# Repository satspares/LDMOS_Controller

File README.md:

# LDMOS_Controller
LDMOS Controller with DWIN Display
New October 2026

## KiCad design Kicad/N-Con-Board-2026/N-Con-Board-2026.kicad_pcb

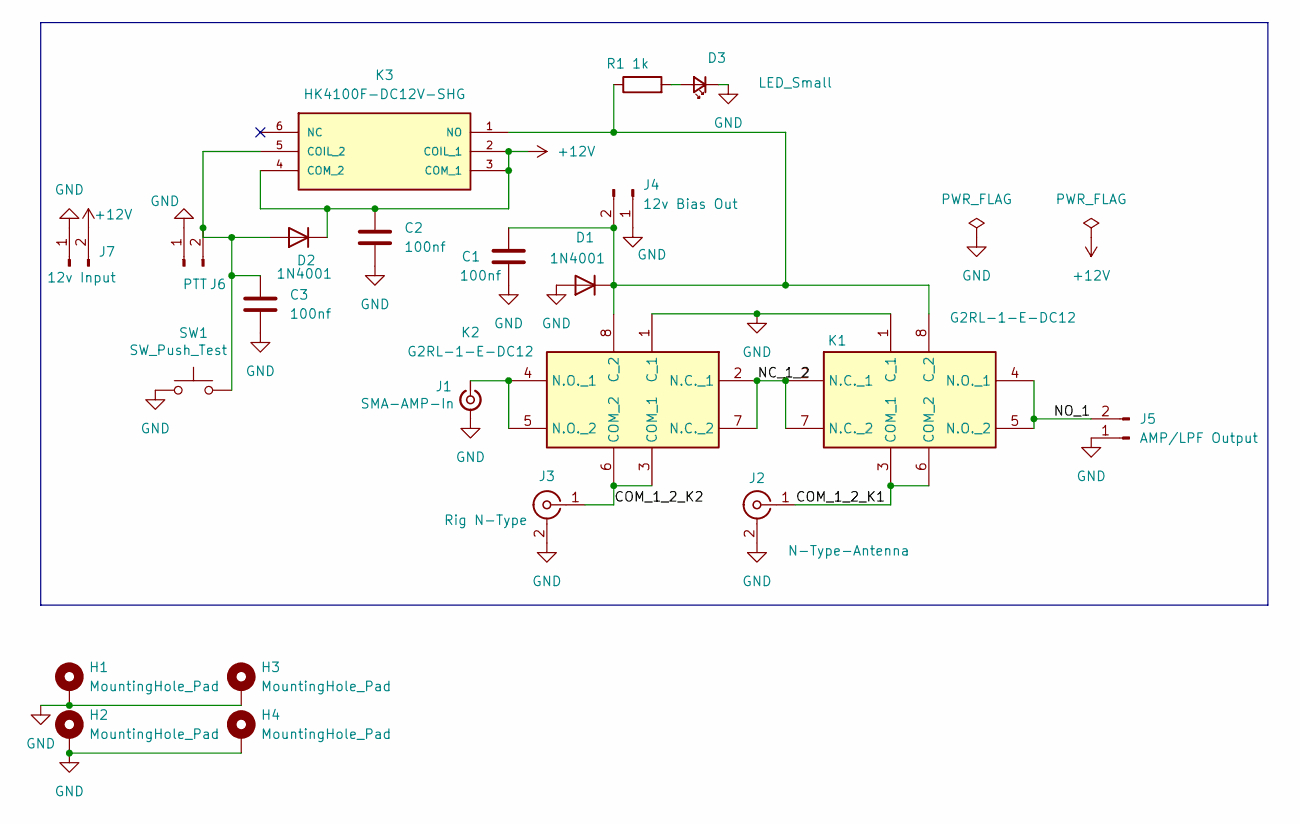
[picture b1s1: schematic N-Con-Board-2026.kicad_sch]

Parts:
C1, C2, C3: 100nf; C_Disc_D6.0mm_W2.5mm_P5.00mm
D1, D2: 1N4001; D_DO-41_SOD81_P10.16mm_Horizontal
D3: LED_Small; LED_D3.0mm
H1, H2, H3, H4: MountingHole_Pad; MountingHole_3.5mm_Pad_Via
J1: SMA-AMP-In; SMA_Amphenol_132134_Vertical
J2: N-Type-Antenna; N_TYPE
J3: Rig N-Type; N_TYPE
J4: 12v Bias Out; JST_EH_B2B-EH-A_1x02_P2.50mm_Vertical
J5: AMP/LPF Output; SolderWirePad_1x02_SMD_11x6mm
J6: PTT; JST_EH_B2B-EH-A_1x02_P2.50mm_Vertical
J7: 12v Input; JST_EH_B2B-EH-A_1x02_P2.50mm_Vertical
K1, K2: G2RL-1-E-DC12; G2RL1EDC24; Mouser Part Number 653-G2RL-1-E-DC12
K3: HK4100F-DC12V-SHG; HK4100FDC5VSHG; MANUFACTURER_PART_NUMBER HK4100F-DC5V-SHG
R1: 1k; R_Axial_DIN0207_L6.3mm_D2.5mm_P7.62mm_Horizontal
SW1: SW_Push_Test; SW_PUSH_6mm

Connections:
+12V: C2.1, D2.1 (K), J7.2, K3.2 (COIL_1), K3.3 (COM_1), K3.4 (COM_2)
/COM_1_2_K1: J2.1 (In), K1.3 (COM_1), K1.6 (COM_2)
/COM_1_2_K2: J3.1 (In), K2.3 (COM_1), K2.6 (COM_2)
/NC_1_2: K1.2 (N.C._1), K1.7 (N.C._2), K2.2 (N.C._1), K2.7 (N.C._2)
/NO_1: J5.2, K1.4 (N.O._1), K1.5 (N.O._2)
GND: C1.2, C2.2, C3.2, D1.2 (A), D3.1 (K), H1.1 (1_1), H2.1 (1_1), H3.1 (1_1), H4.1 (1_1), J1.2 (Ext), J2.2 (Ext), J3.2 (Ext), J4.1, J5.1, J6.1, J7.1, K1.1 (C_1), K2.1 (C_1), SW1.1
unnamed: C1.1, D1.1 (K), J4.2, K1.8 (C_2), K2.8 (C_2), K3.1 (NO), R1.1
unnamed: C3.1, D2.2 (A), J6.2, K3.5 (COIL_2), SW1.2
unnamed: D3.2 (A), R1.2
unnamed: J1.1 (In), K2.4 (N.O._1), K2.5 (N.O._2)

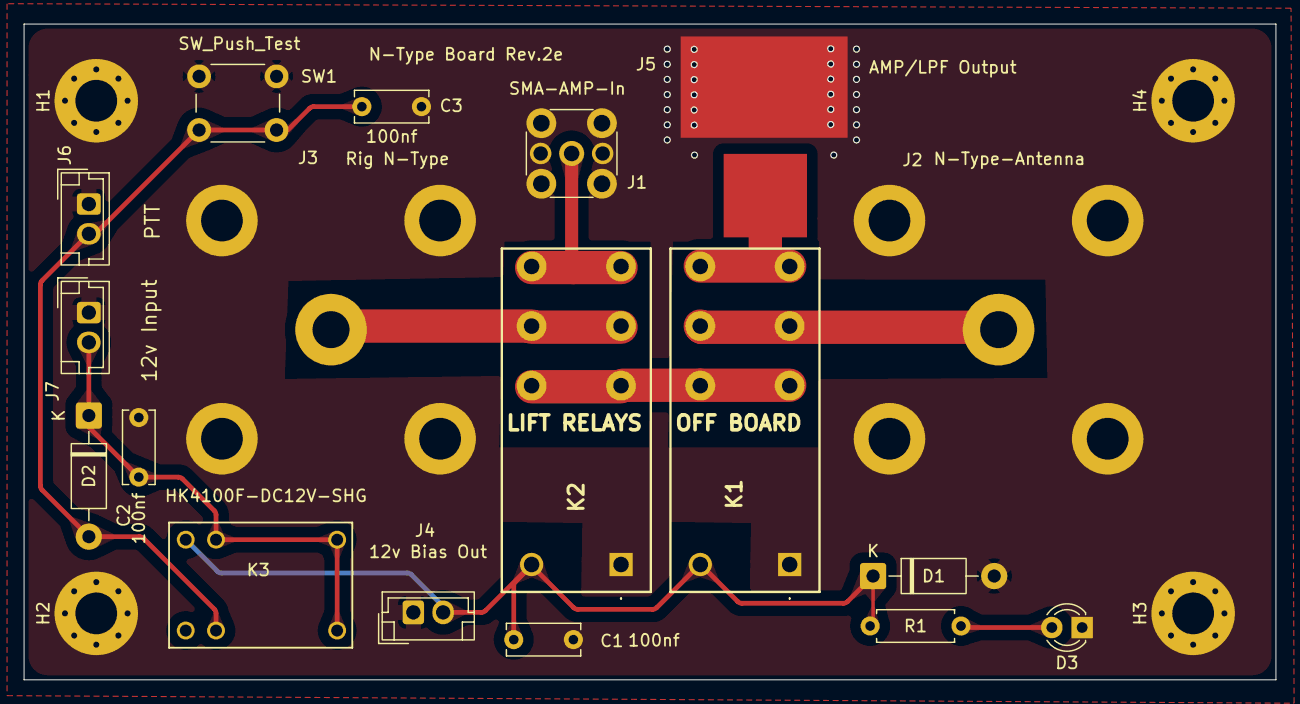
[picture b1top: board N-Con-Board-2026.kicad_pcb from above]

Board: 2 copper layers, 105.0 x 55.0 mm, 22 parts (0 on the bottom side), 10 nets.

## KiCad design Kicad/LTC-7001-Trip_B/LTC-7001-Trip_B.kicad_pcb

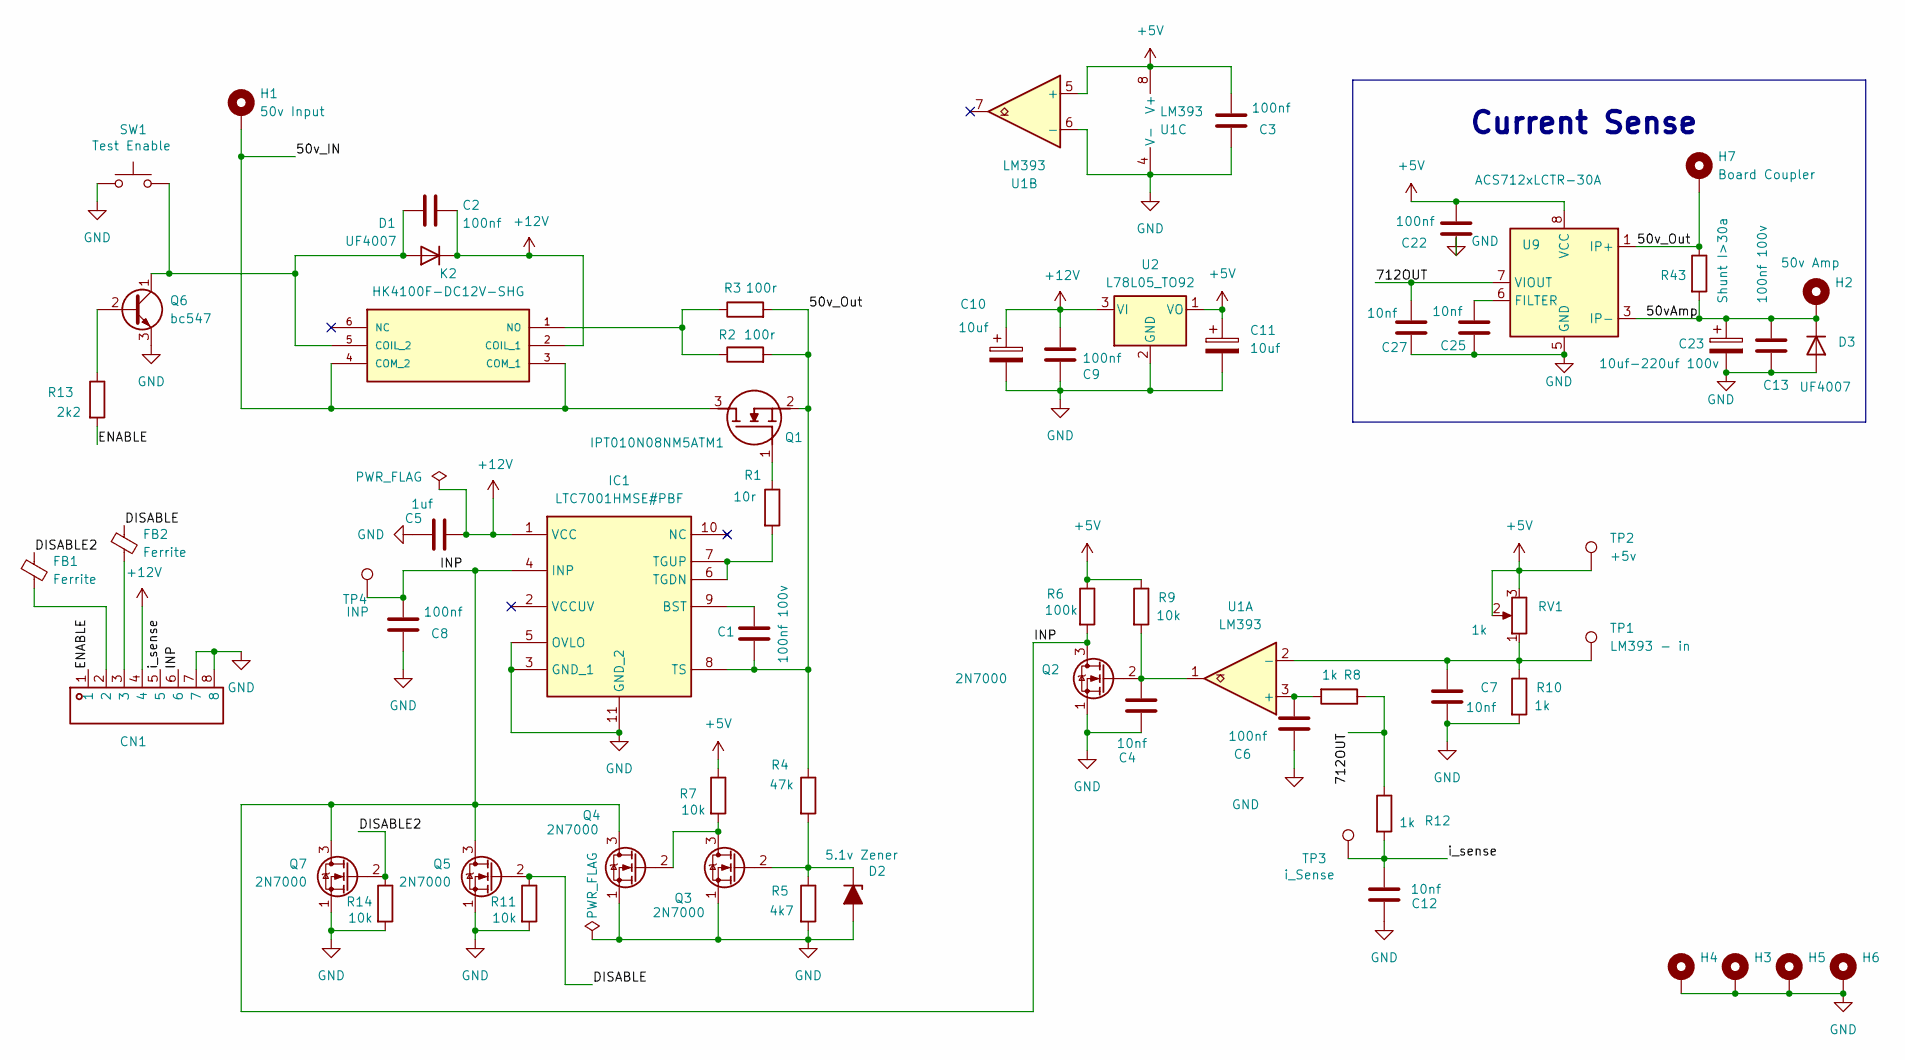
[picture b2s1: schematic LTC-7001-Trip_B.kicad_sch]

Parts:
C1, C13: 100nf 100v; C_Disc_D3.8mm_W2.6mm_P2.50mm
C2, C3, C6, C8, C9, C22: 100nf; C_Disc_D3.8mm_W2.6mm_P2.50mm
C4, C12: 10nf; C_Disc_D3.8mm_W2.6mm_P2.50mm
C5: 1uf; C_Disc_D3.8mm_W2.6mm_P2.50mm
C7, C25, C27: 10nf; C_Disc_D3.4mm_W2.1mm_P2.50mm
C10, C11: 10uf; C_Disc_D3.8mm_W2.6mm_P2.50mm
C23: 10uf-220uf 100v; CP_Radial_D10.0mm_P5.00mm
CN1: CONN-TH_8P-P2.54_KF141R-2.54-8P; Manufacturer Part KF141R-2.54-8P; LCSC Part Name 1x6P 2.54mm 每排P数:8 排数:1
D1, D3: UF4007; D_DO-41_SOD81_P10.16mm_Horizontal
D2: 5.1v Zener; D_DO-35_SOD27_P7.62mm_Horizontal
FB1, FB2: Ferrite; R_1206_3216Metric_Pad1.30x1.75mm_HandSolder
H1: 50v Input; Power-Pad
H2: 50v Amp; Power-Pad
H3, H4, H5, H6: MountingHole_Pad; MountingHole_3.5mm_Pad_Via
H7: Board Coupler; MountingHole_3.5mm_Pad_Via
IC1: LTC7001HMSE#PBF; SOP50P490X110-11N; Manufacturer_Part_Number LTC7001HMSE#PBF; Mouser Part Number 584-LTC7001HMSEPBF
K2: HK4100F-DC12V-SHG; HK4100FDC5VSHG; MANUFACTURER_PART_NUMBER HK4100F-DC5V-SHG
Q1: IPT010N08NM5ATM1; IAUT150N10S5N035ATMA1; Manufacturer_Part_Number FDP083N15A-F102; Mouser Part Number 512-FDP083N15A_F102
Q2, Q3, Q4, Q5, Q7: 2N7000; TO-92-mod2
Q6: bc547; TO-92_HandSolder
R1: 10r; R_Axial_DIN0207_L6.3mm_D2.5mm_P7.62mm_Horizontal
R2, R3: 100r; RESC11050X120N
R4: 47k; R_Axial_DIN0207_L6.3mm_D2.5mm_P7.62mm_Horizontal
R5: 4k7; R_Axial_DIN0207_L6.3mm_D2.5mm_P7.62mm_Horizontal
R6: 100k; R_Axial_DIN0207_L6.3mm_D2.5mm_P7.62mm_Horizontal
R7, R9, R11, R14: 10k; R_Axial_DIN0207_L6.3mm_D2.5mm_P7.62mm_Horizontal
R8, R10, R12: 1k; R_Axial_DIN0207_L6.3mm_D2.5mm_P7.62mm_Horizontal
R13: 2k2; R_Axial_DIN0207_L6.3mm_D2.5mm_P7.62mm_Horizontal
R43: Shunt I>30a; RESC11050X120N
RV1: 1k
SW1: Test Enable; SW_PUSH_6mm
TP1: LM393 - in; TestPoint_THTPad_3.0x3.0mm_Drill1.5mm
TP2: +5v; TestPoint_THTPad_3.0x3.0mm_Drill1.5mm
TP3: i_Sense; TestPoint_THTPad_3.0x3.0mm_Drill1.5mm
TP4: INP; TestPoint_THTPad_3.0x3.0mm_Drill1.5mm
U1: LM393; DIP-8_W7.62mm_Socket
U2: L78L05_TO92; TO-92_Inline-mod
U9: ACS712xLCTR-30A; SOIC-8_3.9x4.9mm_P1.27mm

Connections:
+5V: C3.2, C11.1, C22.1, R6.1, R7.1, R9.1, RV1.2, RV1.3, TP2.1 (1_1), U1.5 (+), U1.8 (V+), U2.1 (VO), U9.8 (VCC)
+12V: C2.2, C5.2, C9.2, C10.1, CN1.4, D1.1 (K), IC1.1 (VCC), K2.2 (COIL_1), U2.3 (VI)
/50vAmp: C13.1, C23.1, D3.1 (K), H2.1 (1_1), R43.2, U9.3 (IP-), U9.4 (IP-)
/50v_IN: H1.1 (1_1), K2.3 (COM_1), K2.4 (COM_2), Q1.3 (S)
/50v_Out: C1.2, H7.1 (1_1), IC1.8 (TS), Q1.2 (D), R2.2, R3.2, R4.1, R43.1, U9.1 (IP+), U9.2 (IP+)
/712OUT: C27.1, R8.1, R12.1, U9.7 (VIOUT)
/DISABLE: FB2.1, Q5.2 (G), R11.1
/DISABLE2: FB1.1, Q7.2 (G), R14.1
/ENABLE: CN1.1, R13.2
/INP: C8.2, CN1.6, IC1.4 (INP), Q2.3 (D), Q4.3 (D), Q5.3 (D), Q7.3 (D), R6.2, TP4.1 (1_1)
/i_sense: C12.1, CN1.5, R12.2, TP3.1 (1_1)
GND: C3.1, C4.1, C5.1, C6.1, C7.1, C8.1, C9.1, C10.2, C11.2, C12.2, C13.2, C22.2, C23.2, C25.1, C27.2, CN1.7, CN1.8, D2.2 (A), D3.2 (A), H3.1 (1_1), H4.1 (1_1), H5.1 (1_1), H6.1 (1_1), IC1.3 (GND_1), IC1.5 (OVLO), IC1.11 (GND_2), Q2.1 (S), Q3.1 (S), Q4.1 (S), Q5.1 (S), Q6.3 (E), Q7.1 (S), R5.2, R10.2, R11.2, R14.2, SW1.1, U1.4 (V-), U1.6 (-), U2.2 (GND), U9.5 (GND)
unnamed: CN1.2, FB1.2
unnamed: CN1.3, FB2.2
unnamed: C2.1, D1.2 (A), K2.5 (COIL_2), Q6.1 (C), SW1.2
unnamed: D2.1 (K), Q3.2 (G), R4.2, R5.1
unnamed: C1.1, IC1.9 (BST)
unnamed: IC1.6 (TGDN), IC1.7 (TGUP), R1.2
unnamed: K2.1 (NO), R2.1, R3.1
unnamed: Q1.1 (G), R1.1
unnamed: C4.2, Q2.2 (G), R9.2, U1.1
unnamed: Q3.3 (D), Q4.2 (G), R7.2
unnamed: Q6.2 (B), R13.1
unnamed: C6.2, R8.2, U1.3 (+)
unnamed: C7.2, R10.1, RV1.1, TP1.1 (1_1), U1.2 (-)
unnamed: C25.2, U9.6 (FILTER)

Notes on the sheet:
Current Sense

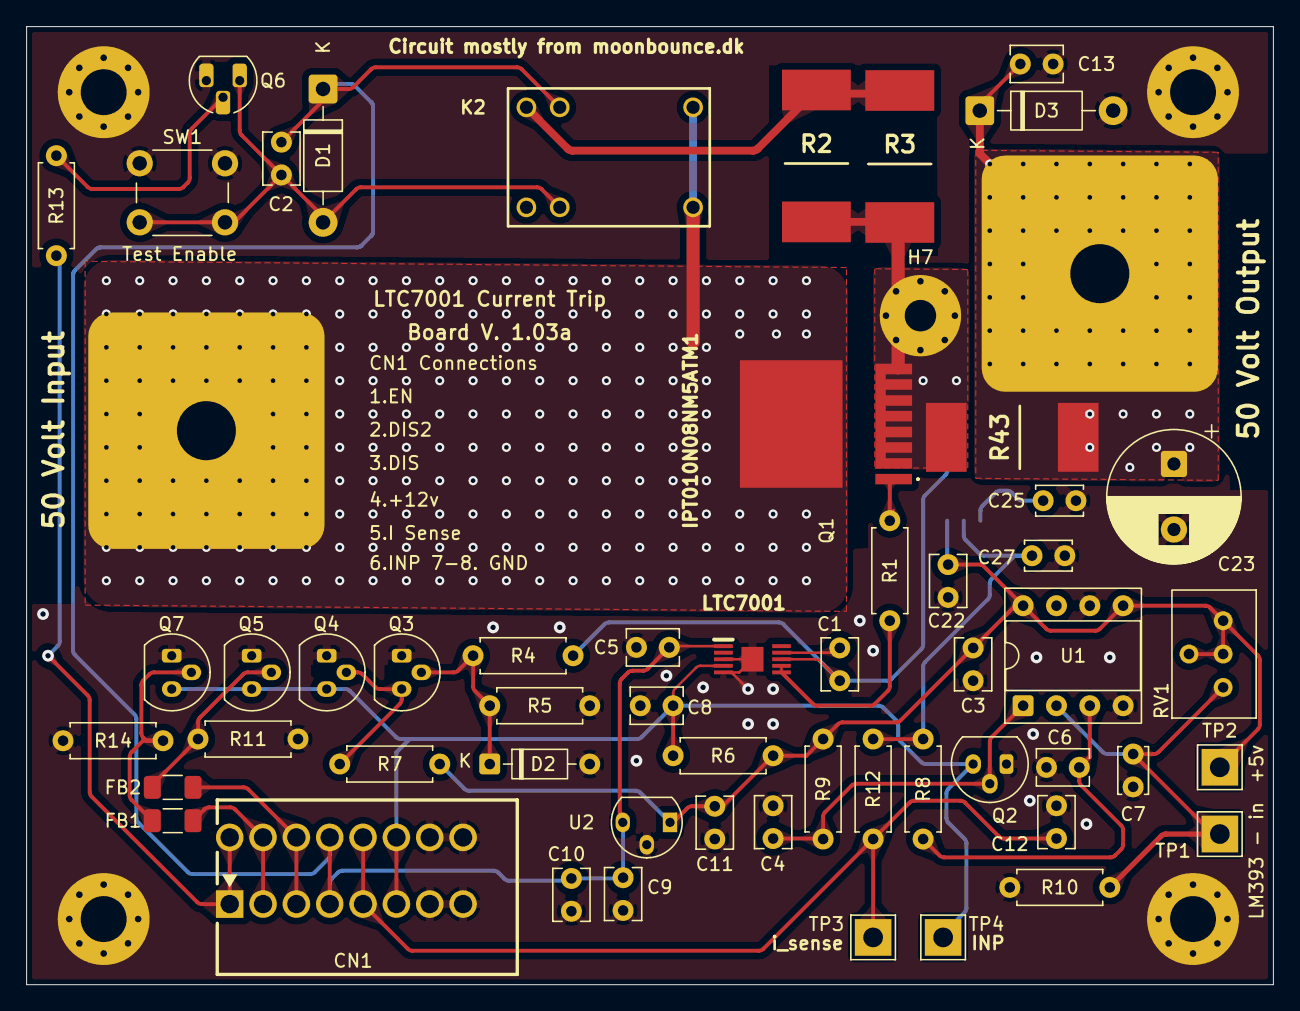
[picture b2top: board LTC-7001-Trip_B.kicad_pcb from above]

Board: 2 copper layers, 95.0 x 73.0 mm, 63 parts (1 on the bottom side), 26 nets.

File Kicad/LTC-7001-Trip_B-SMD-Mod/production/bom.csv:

Designator,Footprint,Quantity,Value,LCSC Part #
"C1, C13",C_Disc_D3.8mm_W2.6mm_P2.50mm,2,100nf 100v,
"C10, C11",C_Disc_D3.8mm_W2.6mm_P2.50mm,2,10uf,
"C12, C4",C_Disc_D3.8mm_W2.6mm_P2.50mm,2,10nf,
"C2, C22, C3, C6, C8, C9",C_Disc_D3.8mm_W2.6mm_P2.50mm,6,100nf,
C23,CP_Radial_D10.0mm_P5.00mm,1,10uf-220uf 100v,
"C25, C27, C7",C_Disc_D3.4mm_W2.1mm_P2.50mm,3,10nf,
C5,C_Disc_D3.8mm_W2.6mm_P2.50mm,1,1uf,
CN1,CONN-TH_8P-P2.54_KF141R-2.54-8P,1,~,
"D1, D3",D_DO-41_SOD81_P10.16mm_Horizontal,2,UF4007,
D2,D_DO-35_SOD27_P7.62mm_Horizontal,1,5.1v Zener,
"FB1, FB2",1206,2,Ferrite,
IC1,SOP50P490X110-11N,1,LTC7001HMSE#PBF,
K2,HK4100FDC5VSHG,1,HK4100F-DC12V-SHG,
Q1,IAUT150N10S5N035ATMA1,1,IPT010N08NM5ATM1,
"Q2, Q3, Q4, Q5, Q7",TO-92-mod2,5,2N7000,
Q6,TO-92_HandSolder,1,bc547,
R1,R_Axial_DIN0207_L6.3mm_D2.5mm_P7.62mm_Horizontal,1,10r,
"R10, R12, R8",R_Axial_DIN0207_L6.3mm_D2.5mm_P7.62mm_Horizontal,3,1k,
"R11, R14, R7, R9",R_Axial_DIN0207_L6.3mm_D2.5mm_P7.62mm_Horizontal,4,10k,
R13,R_Axial_DIN0207_L6.3mm_D2.5mm_P7.62mm_Horizontal,1,2k2,
"R2, R3",RESC11050X120N,2,100r,
R4,R_Axial_DIN0207_L6.3mm_D2.5mm_P7.62mm_Horizontal,1,47k,
R43,RESC11050X120N,1,Shunt I>30a,
R5,R_Axial_DIN0207_L6.3mm_D2.5mm_P7.62mm_Horizontal,1,4k7,
R6,R_Axial_DIN0207_L6.3mm_D2.5mm_P7.62mm_Horizontal,1,100k,
RV1,Potentiometer_Bourns_3296W_Vertical,1,1k,
SW1,SW_PUSH_6mm,1,Test Enable,
TP1,TestPoint_THTPad_3.0x3.0mm_Drill1.5mm,1,LM393 - in,
TP2,TestPoint_THTPad_3.0x3.0mm_Drill1.5mm,1,+5v,
TP3,TestPoint_THTPad_3.0x3.0mm_Drill1.5mm,1,i_Sense,
TP4,TestPoint_THTPad_3.0x3.0mm_Drill1.5mm,1,INP,
U1,SOP-8_3.76x4.96mm_P1.27mm,1,LMV393,
U2,TO-92_Inline-mod,1,L78L05_TO92,
U9,SOIC-8_3.9x4.9mm_P1.27mm,1,ACS712xLCTR-30A,

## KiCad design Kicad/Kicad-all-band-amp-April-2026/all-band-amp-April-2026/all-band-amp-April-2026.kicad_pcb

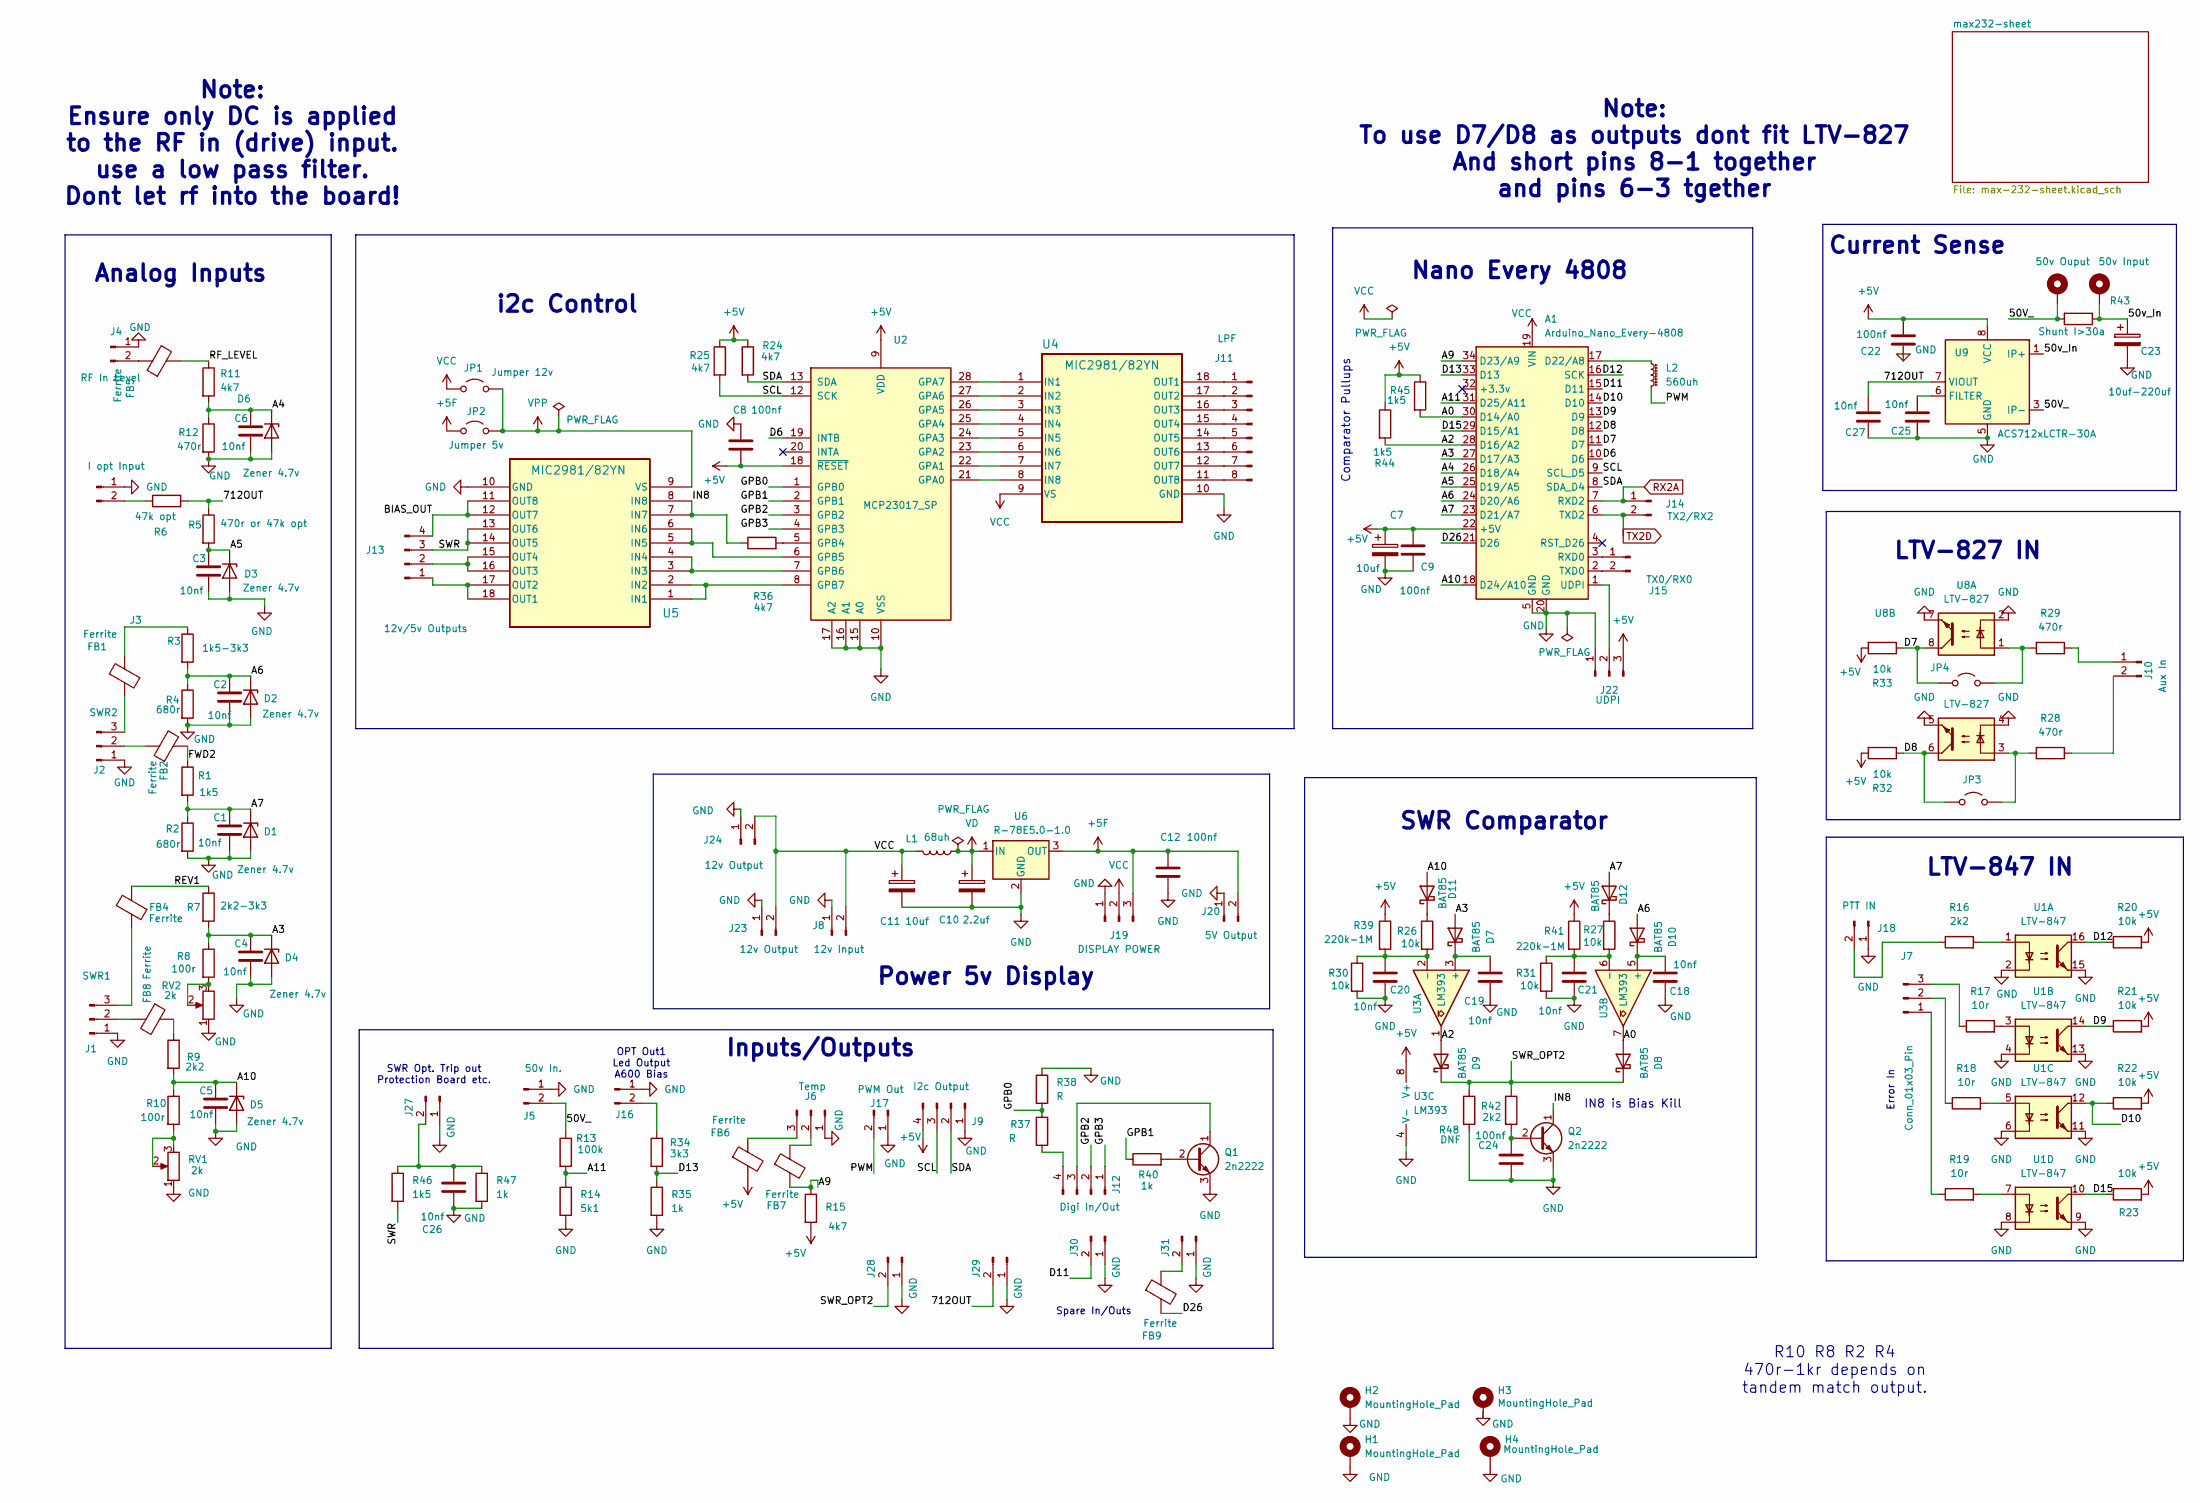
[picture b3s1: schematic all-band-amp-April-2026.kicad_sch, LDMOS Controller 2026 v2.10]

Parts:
A1: Arduino_Nano_Every-4808; DIP-34_W15.24mm
C1, C2, C3, C4, C5, C6, C18, C19, C20, C21, C25, C26, C27: 10nf; C_Disc_D3.4mm_W2.1mm_P2.50mm
C7, C11: 10uf; CP_Radial_D5.0mm_P2.00mm
C8, C9, C12, C22, C24: 100nf; C_Disc_D6.0mm_W2.5mm_P5.00mm
C10: 2.2uf; CP_Radial_D5.0mm_P2.00mm
C23: 10uf-220uf; CP_Radial_D10.0mm_P5.00mm
D1, D2, D3, D4, D5, D6: Zener 4.7v; D_DO-35_SOD27_P7.62mm_Horizontal
D7, D8, D9, D10, D11, D12: BAT85; D_DO-35_SOD27_P7.62mm_Horizontal
FB1, FB2, FB4, FB5, FB6, FB7, FB8, FB9: Ferrite; R_1206_3216Metric_Pad1.30x1.75mm_HandSolder-mod
H1, H2, H3, H4: MountingHole_Pad; MountingHole_3.5mm_Pad_Via
H5: 50v Ouput; PowerPad9mm
H6: 50v Input; PowerPad9mm
J1: SWR1; JST_EH_B3B-EH-A_1x03_P2.50mm_Vertical-mod2
J2: SWR2; JST_EH_B3B-EH-A_1x03_P2.50mm_Vertical-mod2
J3: I opt Input; JST_EH_B2B-EH-A_1x02_P2.50mm_Vertical-Mod
J4: RF In Level; JST_EH_B2B-EH-A_1x02_P2.50mm_Vertical-Mod
J5, J16: 50v In.; JST_EH_B2B-EH-A_1x02_P2.50mm_Vertical-Mod
J6: Temp; JST_EH_B3B-EH-A_1x03_P2.50mm_Vertical-mod2
J7: Conn_01x03_Pin; JST_EH_B3B-EH-A_1x03_P2.50mm_Vertical-mod2
J8: 12v Input; JST_EH_B2B-EH-A_1x02_P2.50mm_Vertical-Mod
J9: I2c Output; JST_EH_B4B-EH-A_1x04_P2.50mm_Vertical-mod2
J10: Aux In; JST_EH_B2B-EH-A_1x02_P2.50mm_Vertical-Mod
J11: LPF; JST_EH_B8B-EH-A_1x08_P2.50mm_Vertical
J12: Digi In/Out; JST_EH_B4B-EH-A_1x04_P2.50mm_Vertical-mod2
J13: 12v/5v Outputs; JST_EH_B4B-EH-A_1x04_P2.50mm_Vertical-mod2
J14: TX2/RX2; JST_EH_B2B-EH-A_1x02_P2.50mm_Vertical-Mod
J15: TX0/RX0; JST_EH_B2B-EH-A_1x02_P2.50mm_Vertical-Mod
J17: PWM Out; JST_EH_B2B-EH-A_1x02_P2.50mm_Vertical-Mod
J18: PTT IN; JST_EH_B2B-EH-A_1x02_P2.50mm_Vertical-Mod
J19: DISPLAY POWER; JST_EH_B3B-EH-A_1x03_P2.50mm_Vertical-mod2
J20: 5V Output; JST_EH_B2B-EH-A_1x02_P2.50mm_Vertical-Mod
J22: UDPI; JST_EH_B3B-EH-A_1x03_P2.50mm_Vertical
J23, J24: 12v Output; JST_EH_B2B-EH-A_1x02_P2.50mm_Vertical-Mod
J27, J28, J29, J30, J31: SWR trip out; JST_EH_B2B-EH-A_1x02_P2.50mm_Vertical-Mod
JP1: Jumper 12v; SolderWire-0.5sqmm_1x02_P4.8mm_D0.9mm_OD2.3mm
JP2: Jumper 5v; SolderWire-0.5sqmm_1x02_P4.8mm_D0.9mm_OD2.3mm
JP3, JP4: Jumper_2_Open; SolderJumper-2_P1.3mm_Open_TrianglePad1.0x1.5mm
L1: 68uh; L_Radial_D7.0mm_P3.00mm
L2: 560uh; L_Axial_L5.3mm_D2.2mm_P7.62mm_Horizontal_Vishay_IM-1
Q1, Q2: 2n2222; TO-92_HandSolder
R1, R44, R45, R46: 1k5; R_Axial_DIN0207_L6.3mm_D2.5mm_P7.62mm_Horizontal
R2, R4: 680r; R_Axial_DIN0207_L6.3mm_D2.5mm_P7.62mm_Horizontal
R3: 1k5-3k3; R_Axial_DIN0207_L6.3mm_D2.5mm_P7.62mm_Horizontal
R5: 470r or 47k opt; R_Axial_DIN0207_L6.3mm_D2.5mm_P7.62mm_Horizontal
R6: 47k opt; R_Axial_DIN0207_L6.3mm_D2.5mm_P7.62mm_Horizontal
R7: 2k2-3k3; R_Axial_DIN0207_L6.3mm_D2.5mm_P7.62mm_Horizontal
R8, R10: 100r; R_Axial_DIN0207_L6.3mm_D2.5mm_P7.62mm_Horizontal
R9, R16, R42: 2k2; R_Axial_DIN0207_L6.3mm_D2.5mm_P7.62mm_Horizontal
R11: 4k7; R_Axial_DIN0204_L3.6mm_D1.6mm_P5.08mm_Horizontal
R12: 470r; R_Axial_DIN0204_L3.6mm_D1.6mm_P5.08mm_Horizontal
R13: 100k; R_Axial_DIN0207_L6.3mm_D2.5mm_P7.62mm_Horizontal
R14: 5k1; R_Axial_DIN0207_L6.3mm_D2.5mm_P7.62mm_Horizontal
R15, R24, R25, R36: 4k7; R_Axial_DIN0207_L6.3mm_D2.5mm_P7.62mm_Horizontal
R17, R18, R19: 10r; R_Axial_DIN0207_L6.3mm_D2.5mm_P7.62mm_Horizontal
R20, R21, R22, R23, R26, R27, R30, R31, R32, R33: 10k; R_Axial_DIN0207_L6.3mm_D2.5mm_P7.62mm_Horizontal
R28, R29: 470r; R_Axial_DIN0207_L6.3mm_D2.5mm_P7.62mm_Horizontal
R34: 3k3; R_Axial_DIN0207_L6.3mm_D2.5mm_P7.62mm_Horizontal
R35, R40, R47: 1k; R_Axial_DIN0207_L6.3mm_D2.5mm_P7.62mm_Horizontal
R37, R38: R; R_Axial_DIN0207_L6.3mm_D2.5mm_P7.62mm_Horizontal
R39, R41: 220k-1M; R_Axial_DIN0207_L6.3mm_D2.5mm_P7.62mm_Horizontal
R43: Shunt I>30a; CHSA3920R0003F-MOD
R48: DNF; R_Axial_DIN0207_L6.3mm_D2.5mm_P7.62mm_Horizontal
RV1, RV2: 2k; Potentiometer_Bourns_3299Y_Vertical
U1: LTV-847; DIP-16_W7.62mm
U2: MCP23017_SP; DIP-28_W7.62mm
U3: LM393; DIP-8_W7.62mm
U4, U5: MIC2981/82YN; DIP-18_W7.62mm_Socket
U6: R-78E5.0-1.0; Converter_DCDC_RECOM_R-78E-0.5_THT
U8: LTV-827; DIP-8_W7.62mm
U9: ACS712xLCTR-30A; SOIC-8_3.9x4.9mm_P1.27mm

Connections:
+5F: C12.1, J19.3, J20.2, JP2.1 (A), U6.3 (OUT); also elsewhere on the board
+5V: A1.22 (+5V), C7.1, C8.2, C9.1, C22.1, FB6.2, J9.4, J22.3, R15.2, R20.2, R21.2, R22.2, R23.2, R24.1, R25.1, R32.2, R33.2, R39.1, R41.1, R44.1, R45.1, U2.9 (VDD), U2.18 (~RESET), U3.8 (V+), U9.8 (VCC)
/50V_: H5.1 (1_1), J5.2, R13.1, R43.2, U9.3 (IP-), U9.4 (IP-)
/50v_In: C23.1, H6.1 (1_1), R43.1, U9.1 (IP+), U9.2 (IP+)
/712OUT: C27.1, J29.2, R5.1, R6.2, U9.7 (VIOUT)
/A0: A1.30 (D14/A0), D8.2 (A), R45.2, U3.7
/A2: A1.28 (D16/A2), D9.2 (A), R44.2, U3.1
/A3: A1.27 (D17/A3), C4.1, D4.1 (K), D7.2 (A), R7.2, R8.1
/A4: A1.26 (D18/A4), C6.1, D6.1 (K), R11.2, R12.1
/A5: A1.25 (D19/A5), C3.1, D3.1 (K), R5.2
/A6: A1.24 (D20/A6), C2.1, D2.1 (K), D10.2 (A), R3.2, R4.1
/A7: A1.23 (D21/A7), C1.1, D1.1 (K), D12.2 (A), R1.2, R2.1
/A9: A1.34 (D23/A9), FB7.2, R15.1
/A10: A1.18 (D24/A10), C5.1, D5.1 (K), D11.2 (A), R9.2, R10.1
/A11: A1.31 (D25/A11), R13.2, R14.1
/BIAS_OUT: J13.4, U5.11 (OUT8), U5.12 (OUT7)
/D6: A1.10 (D6), U2.19 (INTB)
/D7: A1.11 (D7), JP4.1 (A), R33.1, U8.8
/D8: A1.12 (D8), JP3.1 (A), R32.1, U8.6
/D9: A1.13 (D9), R21.1, U1.14
/D10: A1.14 (D10), R22.1, U1.12
/D11: A1.15 (D11), J30.2
/D12: A1.16 (SCK), R20.1, U1.16
/D13: A1.33 (D13), R34.2, R35.1
/D15: A1.29 (D15/A1), R23.1, U1.10
/D26: A1.21 (D26), FB9.2
/FWD2: FB2.2, R1.1
/GPB0: R37.1, R38.2, U2.1 (GPB0)
/GPB1: R40.1, U2.2 (GPB1)
/GPB2: J12.2, U2.3 (GPB2)
/GPB3: J12.1, U2.4 (GPB3)
/IN8: Q2.1 (C), R36.1, U5.7 (IN7), U5.8 (IN8)
/PWM: J17.2, L2.2
/REV1: FB4.2, R7.1
/RF_LEVEL: FB5.2, R11.1
/SCL: A1.9 (SCL_D5), J9.3, R25.2, U2.12 (SCK)
/SDA: A1.8 (SDA_D4), J9.2, R24.2, U2.13 (SDA)
/SWR: J13.3, R46.2, U5.13 (OUT6), U5.14 (OUT5)
/SWR_OPT2: D8.1 (K), D9.1 (K), J28.2, R42.1, R48.1
GND: A1.5 (GND), A1.20 (GND), C1.2, C2.2, C3.2, C4.2, C5.2, C6.2, C7.2, C8.1, C9.2, C10.2, C11.2, C12.2, C18.1, C19.2, C20.2, C21.2, C22.2, C23.2, C24.2, C25.1, C26.2, C27.2, D1.2 (A), D2.2 (A), D3.2 (A), D4.2 (A), D5.2 (A), D6.2 (A), H1.1 (1_1), H2.1 (1_1), H3.1 (1_1), H4.1 (1_1), J1.1, J2.1, J3.1, J4.1, J5.1, J6.1, J8.1, J9.1, J16.1, J17.1, J18.1, J19.1, J20.1, J22.1, J23.1, J24.1, J27.1, J28.1, J29.1, J30.1, J31.1, Q1.3 (E), Q2.3 (E), R2.2, R4.2, R12.2, R14.2, R30.2, R31.2, R35.2, R38.1, R47.2, R48.2, RV1.1, RV2.1, U1.2, U1.4, U1.6, U1.8, U1.9, U1.11, U1.13, U1.15, U2.10 (VSS), U2.15 (A0), U2.16 (A1), U2.17 (A2), U3.4 (V-), U4.10 (GND), U5.10 (GND), U6.2 (GND), U8.2, U8.4, U8.5, U8.7, U9.5 (GND); also elsewhere on the board
unnamed: A1.17 (D22/A8), L2.1
unnamed: A1.3 (RXD0), J15.1
unnamed: A1.2 (TXD0), J15.2
unnamed: A1.1 (UDPI), J22.2
unnamed: C19.1, D7.1 (K), U3.3 (+)
unnamed: C18.2, D10.1 (K), U3.5 (+)
unnamed: D11.1 (K), R26.1
unnamed: D12.1 (K), R27.1
unnamed: FB1.1, R3.1
unnamed: FB8.1, R9.1
unnamed: FB8.2, J1.2
unnamed: FB4.1, J1.3
unnamed: FB2.1, J2.2
unnamed: FB1.2, J2.3
unnamed: J3.2, R6.1
unnamed: FB5.1, J4.2
unnamed: FB7.1, J6.2
unnamed: FB6.1, J6.3
unnamed: J7.1, R19.1
unnamed: J7.2, R18.1
unnamed: J7.3, R17.1
unnamed: J10.1, R29.1
unnamed: J10.2, R28.1
unnamed: J11.1, U4.18 (OUT1)
unnamed: J11.2, U4.17 (OUT2)
unnamed: J11.3, U4.16 (OUT3)
unnamed: J11.4, U4.15 (OUT4)
unnamed: J11.5, U4.14 (OUT5)
unnamed: J11.6, U4.13 (OUT6)
unnamed: J11.7, U4.12 (OUT7)
unnamed: J11.8, U4.11 (OUT8)
unnamed: J12.3, Q1.1 (C)
unnamed: J12.4, R37.2
unnamed: J13.1, U5.17 (OUT2), U5.18 (OUT1)
unnamed: J13.2, U5.15 (OUT4), U5.16 (OUT3)
unnamed: J16.2, R34.1
unnamed: J18.2, R16.1
unnamed: C26.1, J27.2, R46.1, R47.1
unnamed: FB9.1, J31.2
unnamed: JP3.2 (B), R28.2, U8.3
unnamed: JP4.2 (B), R29.2, U8.1
unnamed: Q1.2 (B), R40.2
unnamed: C24.1, Q2.2 (B), R42.2
unnamed: R8.2, RV2.2, RV2.3
unnamed: R10.2, RV1.2, RV1.3
unnamed: R16.2, U1.1
unnamed: R17.2, U1.3
unnamed: R18.2, U1.5
unnamed: R19.2, U1.7
unnamed: U2.21 (GPA0), U4.8 (IN8)
unnamed: U2.22 (GPA1), U4.7 (IN7)
unnamed: U2.23 (GPA2), U4.6 (IN6)
unnamed: U2.24 (GPA3), U4.5 (IN5)
unnamed: U2.25 (GPA4), U4.4 (IN4)
unnamed: U2.26 (GPA5), U4.3 (IN3)
unnamed: U2.27 (GPA6), U4.2 (IN2)
unnamed: U2.28 (GPA7), U4.1 (IN1)
unnamed: R36.2, U2.5 (GPB4)
unnamed: U2.6 (GPB5), U5.5 (IN5), U5.6 (IN6)
unnamed: U2.7 (GPB6), U5.3 (IN3), U5.4 (IN4)
unnamed: U2.8 (GPB7), U5.1 (IN1), U5.2 (IN2)
unnamed: C20.1, R26.2, R30.1, R39.2, U3.2 (-)
unnamed: C21.1, R27.2, R31.1, R41.2, U3.6 (-)
unnamed: C25.2, U9.6 (FILTER)
RX2A: A1.7 (RXD2), J14.1; also elsewhere on the board
TX2D: A1.6 (TXD2), J14.2; also elsewhere on the board
VCC: A1.19 (VIN), C11.1, J8.2, J19.2, J23.2, J24.2, JP1.1 (A), L1.2, U4.9 (VS)
VD: C10.1, L1.1, U6.1 (IN)
VPP: JP1.2 (B), JP2.2 (B), U5.9 (VS)

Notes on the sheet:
SWR Opt. Trip out Protection Board etc.
LTV-847 IN
Note: Ensure only DC is applied to the RF in (drive) input. use a low pass filter. Dont let rf into the board!
Analog Inputs
Inputs/Outputs
Current Sense
OPT Out1 Led Output A600 Bias
Spare In/Outs
Note: To use D7/D8 as outputs dont fit LTV-827 And short pins 8-1 together and pins 6-3 tgether
Nano Every 4808
SWR Comparator
R10 R8 R2 R4 470r-1kr depends on tandem match output.
i2c Control
LTV-827 IN
Error In
IN8 is Bias Kill
Power 5v Display
Comparator Pullups

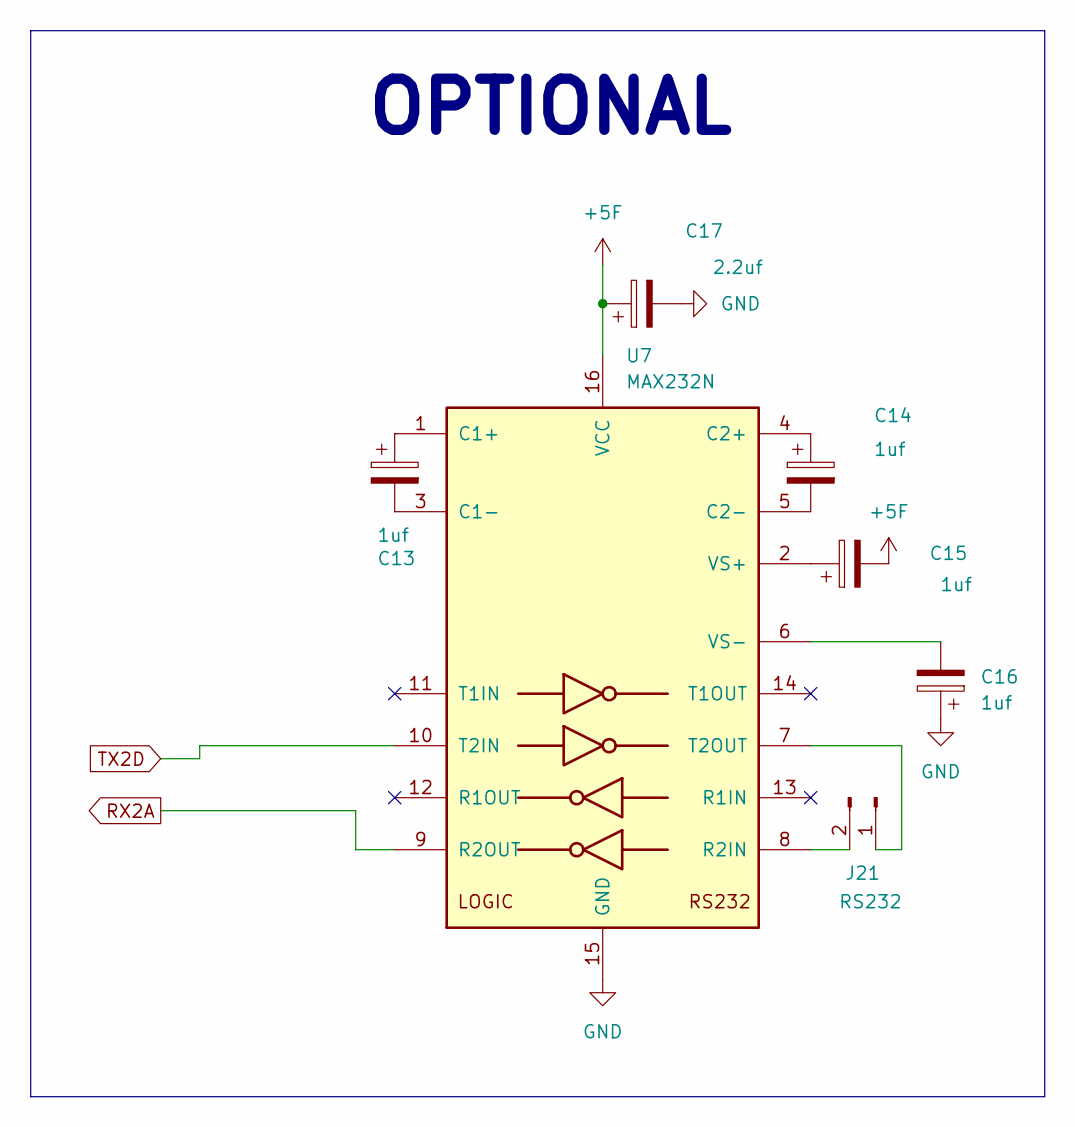
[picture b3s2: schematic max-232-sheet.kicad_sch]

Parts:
C13, C14, C15, C16: 1uf; CP_Radial_D5.0mm_P2.00mm
C17: 2.2uf; CP_Radial_D5.0mm_P2.00mm
J21: RS232; JST_EH_B2B-EH-A_1x02_P2.50mm_Vertical-Mod
U7: MAX232N; DIP-16_W7.62mm

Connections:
+5F: C15.2, C17.1, U7.16 (VCC); also elsewhere on the board
GND: C16.1, C17.2, U7.15 (GND); also elsewhere on the board
unnamed: J21.1, U7.7 (T2OUT)
unnamed: J21.2, U7.8 (R2IN)
unnamed: C13.1, U7.1 (C1+)
unnamed: C13.2, U7.3 (C1-)
unnamed: C14.1, U7.4 (C2+)
unnamed: C14.2, U7.5 (C2-)
unnamed: C15.1, U7.2 (VS+)
unnamed: C16.2, U7.6 (VS-)
RX2A: U7.9 (R2OUT); also elsewhere on the board
TX2D: U7.10 (T2IN); also elsewhere on the board

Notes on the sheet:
OPTIONAL
